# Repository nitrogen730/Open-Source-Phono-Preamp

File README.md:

# Open-Source-Phono-Preamp
an open source phono preamp.

schematic done ^_^
pcb not done yet >_<

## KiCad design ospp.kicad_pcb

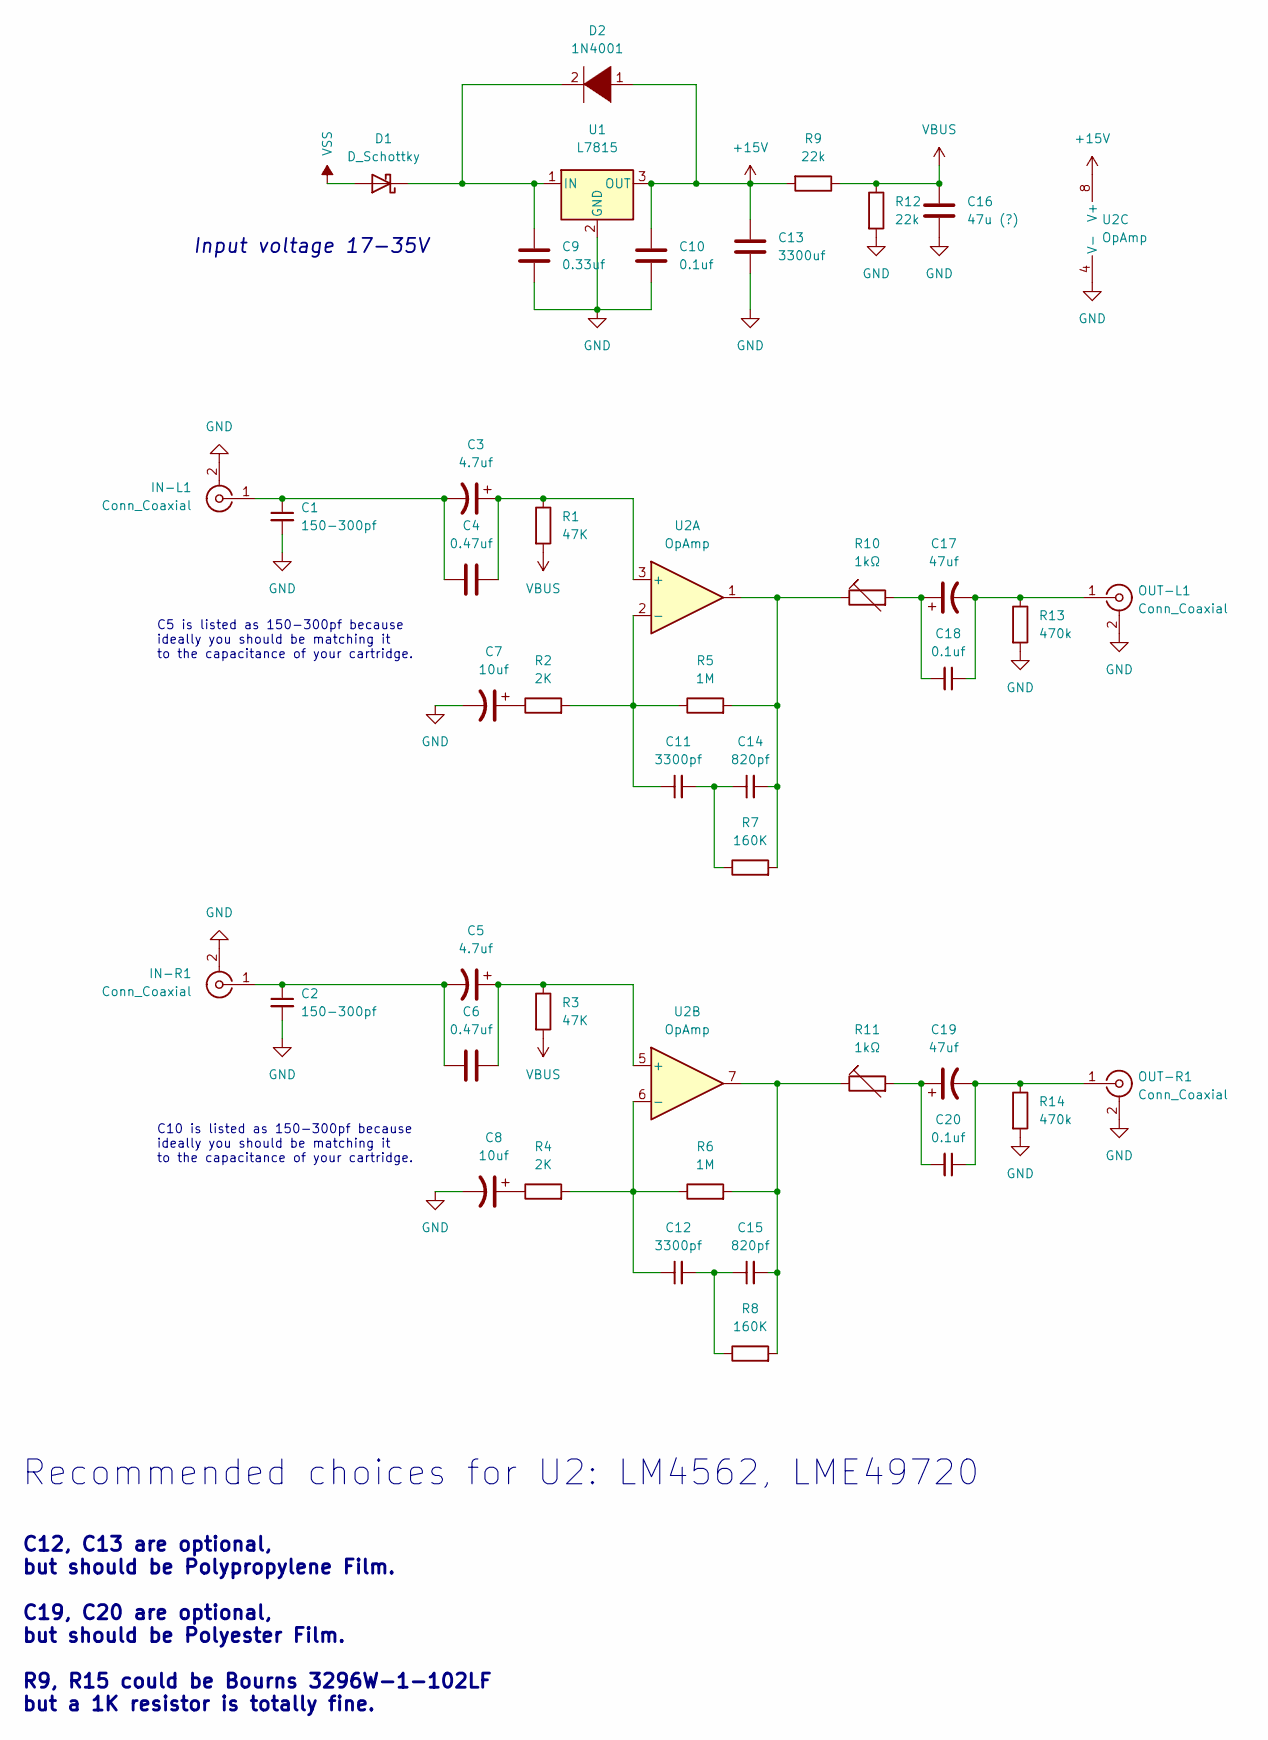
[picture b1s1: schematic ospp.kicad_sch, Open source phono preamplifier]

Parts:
C1, C2: 150-300pf; C_Disc_D9.0mm_W5.0mm_P7.50mm
C3, C5: 4.7uf; C_Disc_D9.0mm_W5.0mm_P7.50mm
C4, C6: 0.47uf; C_Disc_D9.0mm_W5.0mm_P7.50mm
C7: 10uf; C_Rect_L7.2mm_W3.0mm_P5.00mm_FKS2_FKP2_MKS2_MKP2
C8: 10uf; C_Radial_D10.0mm_H12.5mm_P5.00mm
C9: 0.33uf; C_Disc_D9.0mm_W5.0mm_P7.50mm
C10, C18, C20: 0.1uf; C_Disc_D9.0mm_W5.0mm_P7.50mm
C11, C12: 3300pf; C_Radial_D10.0mm_H12.5mm_P5.00mm
C13: 3300uf; C_Radial_D18.0mm_H35.5mm_P7.50mm
C14, C15: 820pf; C_Radial_D10.0mm_H12.5mm_P5.00mm
C16: 47u (?); C_Rect_L7.2mm_W3.0mm_P5.00mm_FKS2_FKP2_MKS2_MKP2
C17, C19: 47uf; C_Radial_D12.5mm_H20.0mm_P5.00mm
D1: D_Schottky; D_DO-201AD_P12.70mm_Horizontal
D2: 1N4001; D_DO-41_SOD81_P7.62mm_Horizontal
IN-L1: Conn_Coaxial; PinSocket_1x02_P2.54mm_Vertical
IN-R1: Conn_Coaxial; PinSocket_1x02_P2.54mm_Vertical
OUT-L1: Conn_Coaxial; PinSocket_1x02_P2.54mm_Vertical
OUT-R1: Conn_Coaxial; PinSocket_1x02_P2.54mm_Vertical
R1, R3: 47K; R_Box_L8.4mm_W2.5mm_P5.08mm
R2, R4: 2K; R_Box_L8.4mm_W2.5mm_P5.08mm
R5, R6: 1M; R_Box_L8.4mm_W2.5mm_P5.08mm
R7, R8: 160K; R_Box_L8.4mm_W2.5mm_P5.08mm
R9, R12: 22k; R_Box_L8.4mm_W2.5mm_P5.08mm
R10, R11: 1kΩ; R_Box_L8.4mm_W2.5mm_P5.08mm
R13, R14: 470k; R_Box_L8.4mm_W2.5mm_P5.08mm
U1: L7815; TO-220-3_Horizontal_TabUp
U2: OpAmp; DIP-8_W10.16mm_LongPads

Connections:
+15V: C10.1, C13.1, D2.1 (K), R9.2, U1.3 (OUT), U2.8 (V+)
GND: C1.2, C2.2, C7.2, C8.2, C9.2, C10.2, C13.2, C16.2, IN-L1.2 (Ext), IN-R1.2 (Ext), OUT-L1.2 (Ext), OUT-R1.2 (Ext), R12.2, R13.2, R14.2, U1.2 (GND), U2.4 (V-)
unnamed: C1.1, C3.2, C4.1, IN-L1.1 (In)
unnamed: C2.1, C5.2, C6.1, IN-R1.1 (In)
unnamed: C3.1, C4.2, R1.1, U2.3 (+)
unnamed: C5.1, C6.2, R3.1, U2.5 (+)
unnamed: C7.1, R2.1
unnamed: C8.1, R4.1
unnamed: C9.1, D1.1 (K), D2.2 (A), U1.1 (IN)
unnamed: C11.1, R2.2, R5.1, U2.2 (-)
unnamed: C11.2, C14.1, R7.1
unnamed: C12.1, R4.2, R6.1, U2.6 (-)
unnamed: C12.2, C15.1, R8.1
unnamed: C14.2, R5.2, R7.2, R10.1, U2.1
unnamed: C15.2, R6.2, R8.2, R11.1, U2.7
unnamed: C17.1, C18.2, R10.2
unnamed: C17.2, C18.1, OUT-L1.1 (In), R13.1
unnamed: C19.1, C20.2, R11.2
unnamed: C19.2, C20.1, OUT-R1.1 (In), R14.1
VBUS: C16.1, R1.2, R3.2, R9.1, R12.1
VSS: D1.2 (A); also elsewhere on the board

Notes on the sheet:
C12, C13 are optional, but should be Polypropylene Film. C19, C20 are optional, but should be Polyester Film. R9, R15 could be Bourns 3296W-1-102LF but a 1K resistor is totally fine.
Input voltage 17-35V
C10 is listed as 150-300pf because ideally you should be matching it to the capacitance of your cartridge.
C5 is listed as 150-300pf because ideally you should be matching it to the capacitance of your cartridge.
Recommended choices for U2: LM4562, LME49720

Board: 2 copper layers, 43 parts (0 on the bottom side), 21 nets, no tracks yet.

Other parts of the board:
VSS: DC input; SolderWire-0.75sqmm_1x01_D1.25mm_OD2.3mm

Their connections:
VSS: VSS.1; also elsewhere on the board

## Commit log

2023-03-05 Add files via upload
    Please note the kicad pcb is not finished yet, and the footprints in the pcb and the schematic don't quite match.
